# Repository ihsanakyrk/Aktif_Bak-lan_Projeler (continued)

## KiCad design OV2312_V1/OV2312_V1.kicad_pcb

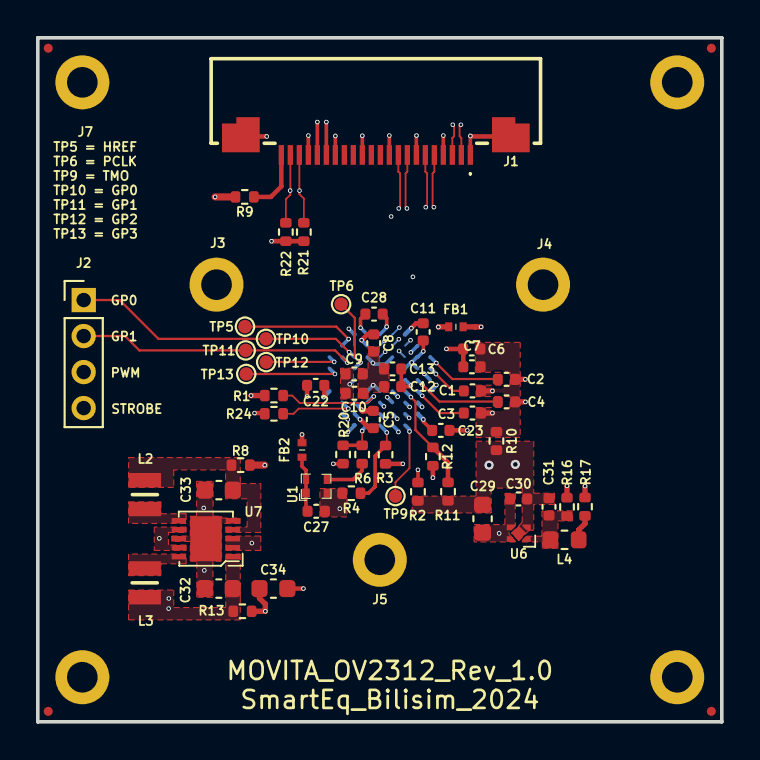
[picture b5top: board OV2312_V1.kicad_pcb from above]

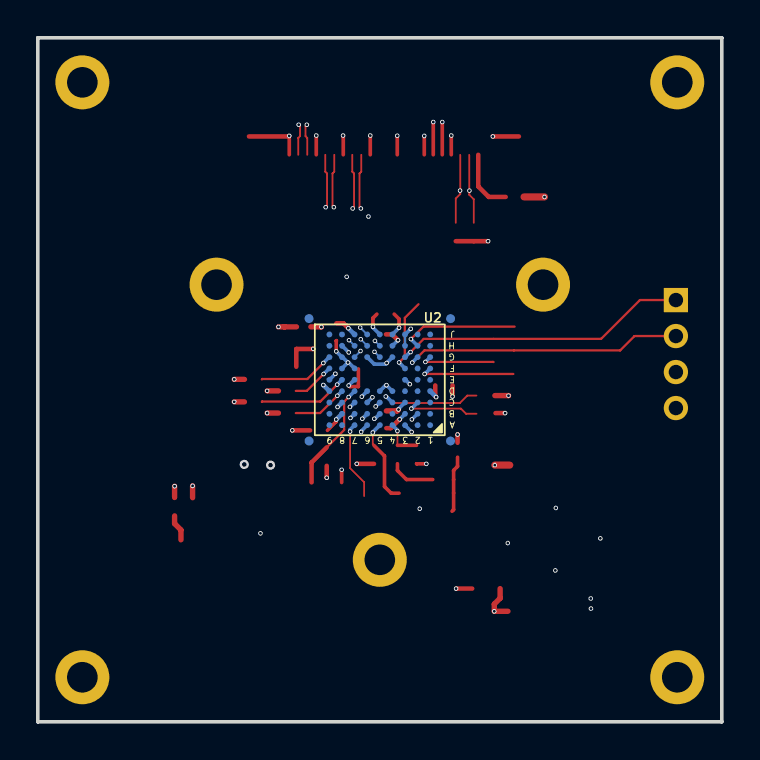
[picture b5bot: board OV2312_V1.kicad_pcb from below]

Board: 6 copper layers, 38.0 x 38.0 mm, 73 parts (5 on the bottom side), 46 nets.

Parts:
C1, C2, C3, C4, C5, C8, C9, C12: 1uF 10V; C_0402_1005Metric
C6, C7, C10, C11, C13, C22, C23, C27, C28: 0.1uF 16V; C_0402_1005Metric
C29, C32, C33, C34: 10uF 10V; C_0603_1608Metric
C30, C31: 1uF 6.3V; C_0402_1005Metric
FB1, FB2: BLM15AG221SN1D; NFZ15SG152SN10B
FID1, FID2, FID3, FID4, FID5, FID6, FID7, FID8: Fiducial; Fiducial_0.5mm_Mask1mm
J1: FFC SOCKET DR_BOTTOM 0.5MM -22P; F32R1A7H111022
J2: DNP; PinHeader_1x04_P2.00mm_Vertical
J3, J4, J5, J6, J7, J8, J9: DNP; Screw
L2, L3: 2.2µH; LQM2MPN1R0NG0L
L4: 3.3uH; L_0603_1608Metric
R1, R2, R8, R9, R10, R13, R16, R17, R24: 0R; R_0402_1005Metric
R3, R11, R20, R21, R22: DNP; R_0402_1005Metric
R4, R12: 10K; R_0402_1005Metric
R6: 22R; R_0402_1005Metric
TP5, TP6, TP9, TP10, TP11, TP12, TP13: DNP; TestPoint_Pad_D0.75
U1: DSC6101MI2A-024.0000T
U2: OV2312
U6: LP5907SNX-2.8/NOPB; X2-SON-4-EP
U7: TPS62423QDRCRQ1; SON50P300X300X100-11N-D

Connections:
3V3: C29.1, C30.1, R9.1, U6.3 (EN), U6.4 (VIN), U7.2 (MODE/DATA), U7.3 (VIN), U7.7 (EN1), U7.9 (EN2)
/CSI2_CLK_N: J1.8, U2.J6 (MCN)
/CSI2_CLK_P: J1.9, U2.H6 (MCP)
/CSI2_D0_N: J1.2, U2.H5 (MDN0)
/CSI2_D0_P: J1.3, U2.G5 (MDP0)
/CSI2_D1_N: J1.5, U2.G7 (MDN1)
/CSI2_D1_P: J1.6, U2.H7 (MDP1)
/EXT_XVCLK: J1.17, R20.2
/FSIN: R24.1, U2.C2 (FSIN/VSYNC)
/GPIO0: J2.1, TP10.1, U2.G3 (D0/GPIO0)
/GPIO1: J2.2, TP11.1, U2.G2 (D1/GPIO1)
/GPIO2: TP12.1, U2.G1 (D2/GPIO2)
/GPIO3: TP13.1, U2.F1 (D3/GPIO3)
/HREF: TP5.1, U2.H2 (HREF)
/PCLK: TP6.1, U2.F3 (PCLK)
/PWM: J2.3, U2.B7 (PWM)
/SCL: J1.20, R21.1, U2.B5 (SCL)
/SDA: J1.21, R22.1, U2.B6 (SDA)
/SID: R3.2, R4.2, U2.A5 (SID)
/STROBE: J2.4, U2.C5 (STROBE)
/TMO: TP9.1, U2.A7 (TMO)
/VH: C4.1, U2.E8 (VH)
/VN1: C1.1, U2.F9 (VN1)
/VN2: C2.1, U2.G9 (VN2)
/VN3: C3.1, U2.D8 (VN3)
/XVCLK: R6.2, R20.1, U2.A4 (XVCLK)
AGND: C1.2, C2.2, C3.2, C4.2, C5.2, C6.2, C7.2, R10.2, U2.B3 (AGND), U2.D9 (AGND)
AVDD: C5.1, C6.1, C7.1, C23.1, R16.1, U2.B8 (AVDD), U2.C3 (AVDD), U2.E9 (AVDD)
AVDD_2V8: C31.1, L4.1, R16.2, U6.1 (VOUT)
DGND: C8.2, C9.2, C10.2, C11.2, C12.2, C13.2, C22.2, C23.2, C27.2, C28.2, C29.2, C30.2, C31.2, C32.2, C33.2, C34.2, J1.1, J1.4, J1.7, J1.10, J1.13, J1.16, J1.19, J1.23, J1.24, J3.1, J4.1, J5.1, J6.1, J7.1, J8.1, J9.1, R1.1, R2.1, R4.1, R10.1, R11.1, U1.2 (GND), U2.C8 (DOGND), U2.D4 (DOGND), U2.D5 (DOGND), U2.F7 (DOGND), U2.F8 (DOGND), U2.G4 (DOGND), U2.G6 (DOGND), U2.G8 (DOGND), U2.J4 (DOGND), U6.2 (GND), U6.5 (EP), U7.5 (DEF_1), U7.8 (GND), U7.11 (PAD)
DOVDD: C8.1, C22.1, C34.1, FB2.1, R3.1, R12.2, R13.1, U2.C6 (DOVDD), U2.D1 (DOVDD), U2.H4 (DOVDD)
DVDD: C9.1, C10.1, C11.1, C28.1, R8.1, U2.A3 (DVDD), U2.A6 (DVDD), U2.B2 (DVDD), U2.D6 (DVDD), U2.E3 (DVDD), U2.H3 (DVDD), U2.H8 (DVDD), U2.J3 (DVDD), U2.J5 (DVDD), U2.J7 (DVDD)
unnamed: J1.18, R24.2
unnamed: J1.22, R9.2
unnamed: C27.1, FB2.2, U1.1 (OE), U1.4 (VDD)
unnamed: R6.1, U1.3 (OUT)
unnamed: C12.1, C13.1, FB1.2, U2.E7 (PVDD)
unnamed: R2.2, U2.C7 (TM)
unnamed: R1.2, U2.C4 (TMCLK)
unnamed: R11.2, R12.1, U2.D7 (XSHUTDOWN)
unnamed: L2.1, U7.6 (SW1)
unnamed: L3.1, U7.10 (SW2)
PVDD: FB1.1, R17.1
PVDD_2V8: L4.2, R17.2
VDD_1V2: C33.1, L2.2, R8.2, U7.4 (FB1)
VDD_1V8: C32.1, L3.2, R13.2, R21.2, R22.2, U7.1 (ADJ2)
